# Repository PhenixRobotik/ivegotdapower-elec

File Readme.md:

# IveGotDaPower, dépôt électronique

Carte alimentation de PhenixRobotik pour la base roulante TheySeeMeRolling.

<div class="alert alert-warning">
    #This project requires KiCAD 5.0 and is not compatible with previous versions (software and libraries).
</div>

# Features

* Dual power input with no-cut switch
  * Battery 6S (24V max)
  * Power supply

* Multiple power outputs
  * Power (direct, 6A)
  * Elec (7.5V ~3A)
  * USB (for Rpi, 2A)
  * …

* Voltage + current instrumentations

* CAN bus

# Idées

* stm32f3
* LiPoBipper (équilibrage) ? (ou direct sur la batterie == plus safe ?)

* Bouton d'arrêt d'urgence qui coupe la puissance moteurs ?

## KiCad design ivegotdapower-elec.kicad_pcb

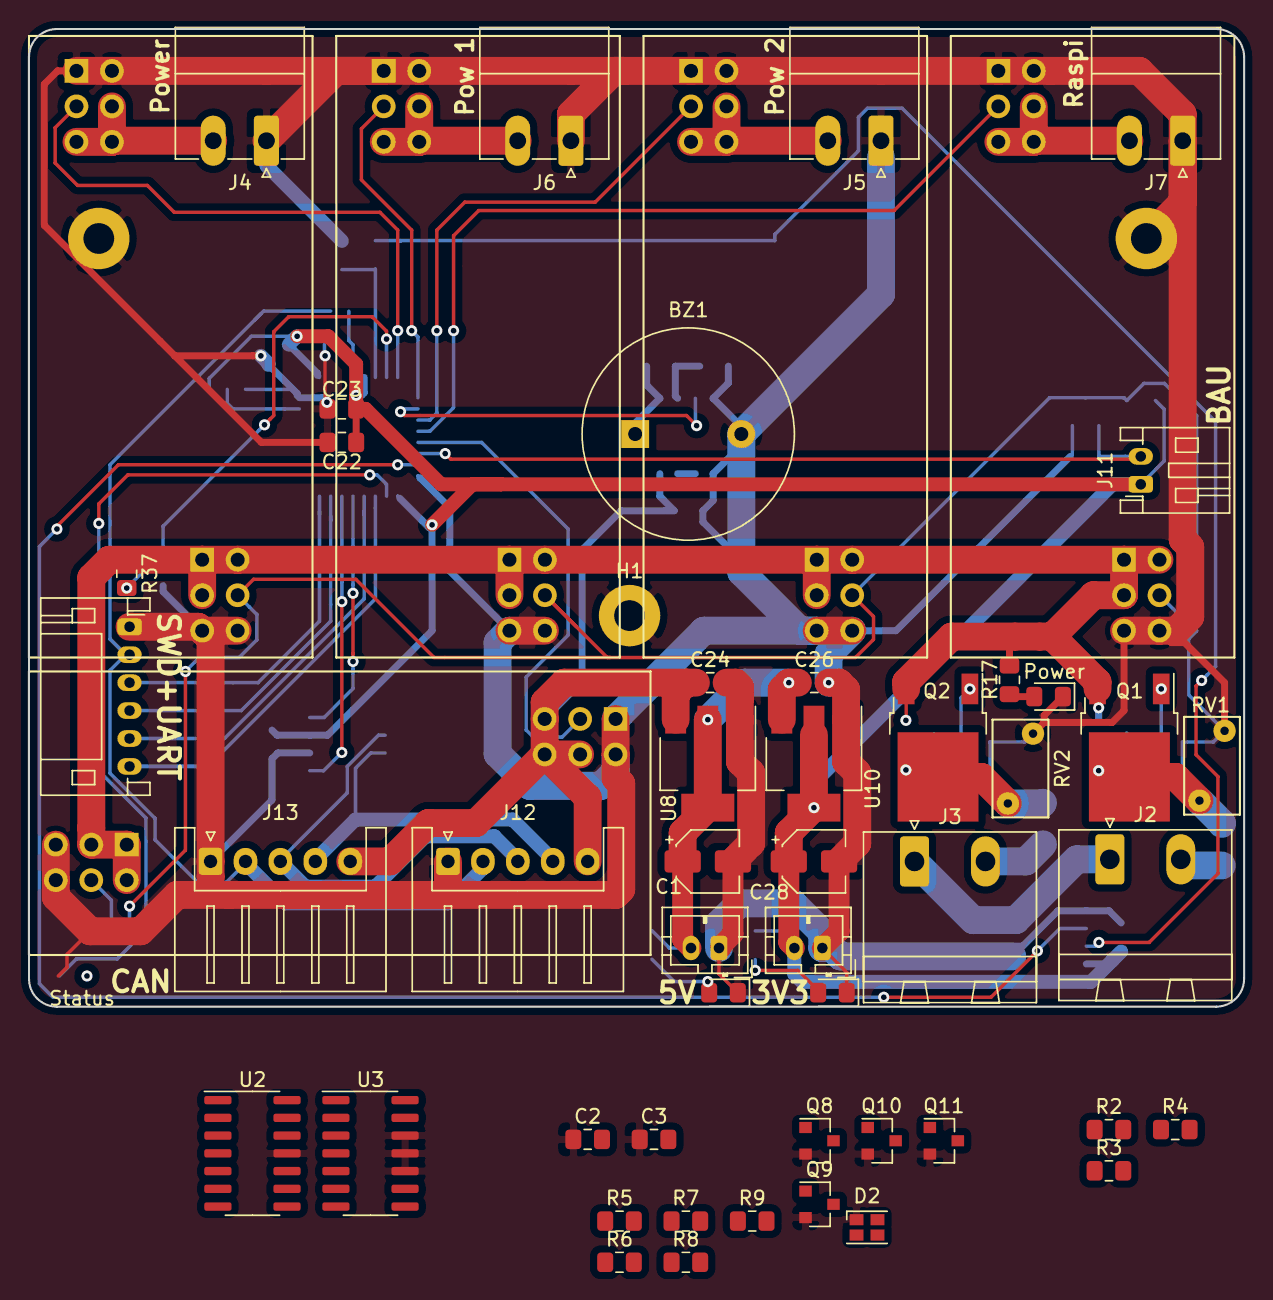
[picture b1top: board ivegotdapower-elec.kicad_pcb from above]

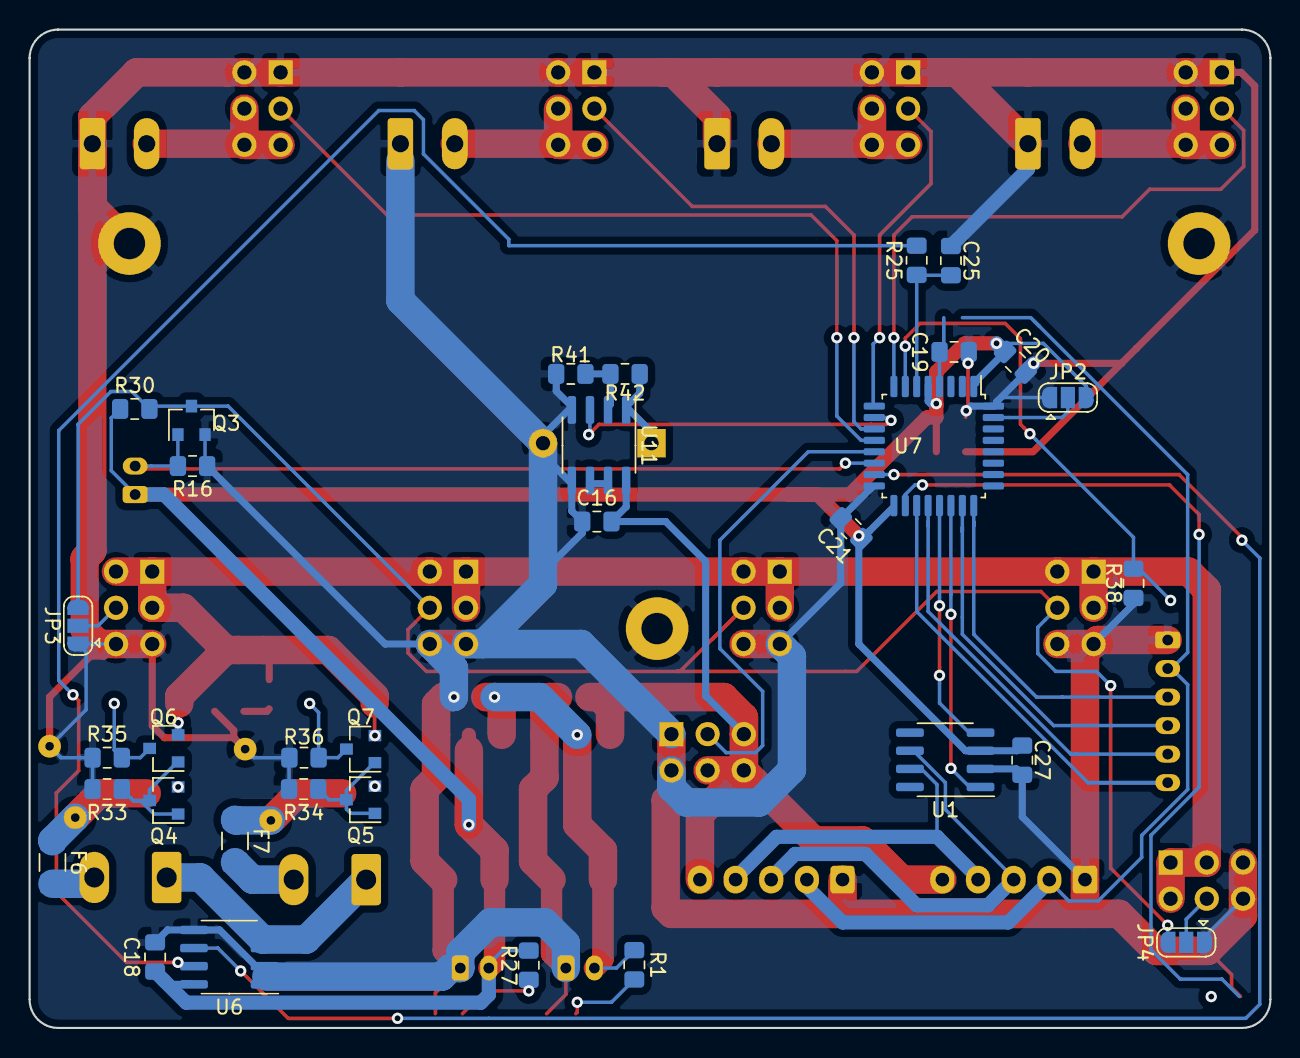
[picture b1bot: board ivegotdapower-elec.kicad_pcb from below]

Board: 2 copper layers, 87.0 x 70.0 mm, 88 parts (33 on the bottom side), 66 nets.

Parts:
B1, B2, B3, B4, B5: board_fille
BZ1: Buzzer; Buzzer_15x7.5RM7.6
C1, C28: 10uF; CP_Elec_4x5.4
C2, C3, C16, C18, C19, C20, C21, C23, C24, C25, C26, C27: 100nF; C_0805_2012Metric_Pad1.15x1.40mm_HandSolder
C22: 4.7uF; C_0805_2012Metric_Pad1.15x1.40mm_HandSolder
D1, D12, D16: LED; LED_0805_2012Metric_Pad1.15x1.40mm_HandSolder
D2: LED_ARGB; LED_Cree-PLCC4_2x2mm_CW
F6, F7: Fuse; Fuse_1206_3216Metric_Pad1.42x1.75mm_HandSolder
H1, H2, H3: MountingHole_Pad; MountingHole_2.2mm_M2_Pad
J1: Conn_Debug; JST_PH_S6B-PH-K_1x06_P2.00mm_Horizontal
J2: Conn_batt; PhoenixContact_MSTBA_2,5_2-G-5,08_1x02_P5.08mm_Horizontal
J3: Conn_alim; PhoenixContact_MSTBA_2,5_2-G-5,08_1x02_P5.08mm_Horizontal
J4: Conn_TSMR; PhoenixContact_MC_1,5_2-G-3.81_1x02_P3.81mm_Horizontal
J5: Conn_POW2; PhoenixContact_MC_1,5_2-G-3.81_1x02_P3.81mm_Horizontal
J6: Conn_POW1; PhoenixContact_MC_1,5_2-G-3.81_1x02_P3.81mm_Horizontal
J7: Conn_RPi; PhoenixContact_MC_1,5_2-G-3.81_1x02_P3.81mm_Horizontal
J8: Conn_+5V; JST_PH_B2B-PH-K_1x02_P2.00mm_Vertical
J10: Conn_+3.3V; JST_PH_B2B-PH-K_1x02_P2.00mm_Vertical
J11: Conn_bau; JST_PH_S2B-PH-K_1x02_P2.00mm_Horizontal
J12, J13: CAN_conn; JST_XH_S05B-XH-A_1x05_P2.50mm_Horizontal
JP2, JP3, JP4: Jumper_NC_Dual; SolderJumper-3_P1.3mm_Open_RoundedPad1.0x1.5mm
Q1, Q2: IRFR5305; TO-252-2
Q3, Q8, Q9, Q10, Q11: BSS138; SOT-23
Q4, Q5, Q6, Q7: MMBT2907A; SOT-23
R1, R17, R25, R27, R30, R33, R34, R35, R36, R41, R42: R; R_0805_2012Metric_Pad1.15x1.40mm_HandSolder
R2: 91; R_0805_2012Metric_Pad1.15x1.40mm_HandSolder
R3: 27; R_0805_2012Metric_Pad1.15x1.40mm_HandSolder
R4: 39; R_0805_2012Metric_Pad1.15x1.40mm_HandSolder
R5, R6, R7, R8, R9: 10k; R_0805_2012Metric_Pad1.15x1.40mm_HandSolder
R16: 1k; R_0805_2012Metric_Pad1.15x1.40mm_HandSolder
R37: 75k; R_0805_2012Metric_Pad1.15x1.40mm_HandSolder
R38: 15k; R_0805_2012Metric_Pad1.15x1.40mm_HandSolder
RV1, RV2: Varistor; RV_Disc_D7mm_W4mm_P5mm
U1: TCAN332; SOIC-8_3.9x4.9mm_P1.27mm
U2, U3: LM324; SOIC-14_3.9x8.7mm_P1.27mm
U6: ACS711xLCTR-12AB; SOIC-8_3.9x4.9mm_P1.27mm
U7: STM32F303K8Tx; LQFP-32_7x7mm_P0.8mm
U8: LD1117S50TR; SOT-223-3_TabPin2
U10: LD1117S33TR; SOT-223-3_TabPin2
U11: LM358; SOIC-8_3.9x4.9mm_P1.27mm

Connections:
+3V3: C18.1, C20.1, C21.1, C22.1, C23.1, C27.2, C28.1, J10.2, J11.1, JP2.3, R5.1, R6.1, R7.1, R8.1, R9.1, R27.1, R30.1, U1.3, U6.8, U7.1, U7.5, U7.17, U10.2
+5V: C1.1, C2.2, C3.2, C26.1, J8.2, R1.1, U2.4, U3.4, U8.2, U10.3
+7.5V: B2.10, B2.11, B2.12, C16.2, C24.1, J12.5, J13.5, U8.3, U11.8
/STM32/Buzzer: U7.10, U11.3
/STM32/CAN_RX: U1.4, U7.21
/STM32/CAN_TX: U1.1, U7.22
/STM32/RX_1: J1.5, U7.20
/STM32/TCK: J1.3, U7.24
/STM32/TMS: J1.4, U7.23
/STM32/TX_1: J1.6, U7.19
/STM32/mes_current: R25.1, U6.7
/STM32/mes_current_fault: U6.6, U7.15
/STM32/mes_protected_TSMR: U2.6, U2.7, U7.8
/STM32/mes_protected_logic: U3.6, U3.7, U7.13
/STM32/mes_protected_pow1: U2.8, U2.9, U7.9
/STM32/mes_protected_pow2: U2.13, U2.14, U7.11
/STM32/mes_protected_raw: U2.1, U2.2, U7.7
/STM32/mes_protected_rpi: U3.1, U3.2, U7.12
/STM32/mes_raw: R37.2, R38.1, U2.3
/STM32/reset_can: J12.2, J13.2, Q8.1, R5.2
/STM32/reset_logic/Reset_MCU: C19.1, Q9.3, Q11.3, R7.2, U7.4
/STM32/reset_swd: J1.2, Q10.1, R8.2
/buck/Logic_mes: B2.9, U3.5
/buck/Pow1_mes: B3.9, U2.10
/buck/Pow2_mes: B4.9, U2.12
/buck/RPi_mes: B1.9, U3.3
/buck/TSMR_mes: B5.9, U2.5
/buck/bau: J11.2, Q3.1, R16.1, U7.14
/buck/~on~-off: B3.4, B4.4, B5.4, JP3.3, JP4.3, Q3.3, R30.2
/power_selection/Valim+: F7.2, J3.2
/power_selection/Vbatt+: F6.2, J2.2
/power_selection/gnd_alims: J2.1, J3.1, U6.3, U6.4
GND: B1.5, B1.6, B1.7, B1.8, B2.5, B2.6, B2.7, B2.8, B3.5, B3.6, B3.7, B3.8, B4.5, B4.6, B4.7, B4.8, B5.5, B5.6, B5.7, B5.8, BZ1.2, C1.2, C2.1, C3.1, C16.1, C18.2, C19.2, C20.2, C21.2, C22.2, C23.2, C24.2, C25.1, C26.2, C27.1, C28.2, D1.1, D2.1, D12.1, D16.1, H1.1, H2.1, H3.1, J1.1, J4.1, J5.1, J6.1, J7.1, J8.1, J10.1, J12.1, J13.1, JP2.1, JP3.1, JP4.1, Q3.2, Q8.2, Q9.2, Q10.2, Q11.2, R16.2, R33.2, R34.2, R35.2, R36.2, R38.2, R41.1, RV1.2, RV2.2, U1.2, U2.11, U3.10, U3.11, U3.12, U6.1, U6.2, U6.5, U7.16, U7.32, U8.1, U10.1, U11.4, U11.5
IN: B1.1, B1.2, B1.3, B2.1, B2.2, B2.3, B3.1, B3.2, B3.3, B4.1, B4.2, B4.3, B5.1, B5.2, B5.3, Q1.3, Q2.3, Q6.2, Q7.2, R17.1, R37.1
unnamed: B1.4, JP3.2
unnamed: B1.10, B1.11, B1.12, J7.2
unnamed: B2.4, JP4.2
unnamed: B3.10, B3.11, B3.12, J6.2
unnamed: B4.10, B4.11, B4.12, J5.2
unnamed: B5.10, B5.11, B5.12, J4.2
unnamed: BZ1.1, R42.2, U11.1
unnamed: C25.2, R25.2, U7.6
unnamed: D1.2, R1.2
unnamed: D2.2, R2.2
unnamed: D2.3, R3.2
unnamed: D2.4, R4.2
unnamed: D12.2, R17.2
unnamed: D16.2, R27.2
unnamed: F6.1, Q1.2, Q4.2, RV1.1
unnamed: F7.1, Q2.2, Q5.2, RV2.1
unnamed: J12.3, J13.3, U1.6
unnamed: J12.4, J13.4, U1.7
unnamed: JP2.2, U7.31
unnamed: Q1.1, Q6.3, R35.1
unnamed: Q2.1, Q7.3, R36.1
unnamed: Q4.1, Q4.3, Q6.1, R33.1
unnamed: Q5.1, Q5.3, Q7.1, R34.1
unnamed: Q8.3, Q9.1, R6.2
unnamed: Q10.3, Q11.1, R9.2
unnamed: R2.1, U7.28
unnamed: R3.1, U7.29
unnamed: R4.1, U7.30
unnamed: R41.2, R42.1, U11.2
unnamed: U3.8, U3.9
unnamed: U3.13, U3.14
unnamed: U11.6, U11.7

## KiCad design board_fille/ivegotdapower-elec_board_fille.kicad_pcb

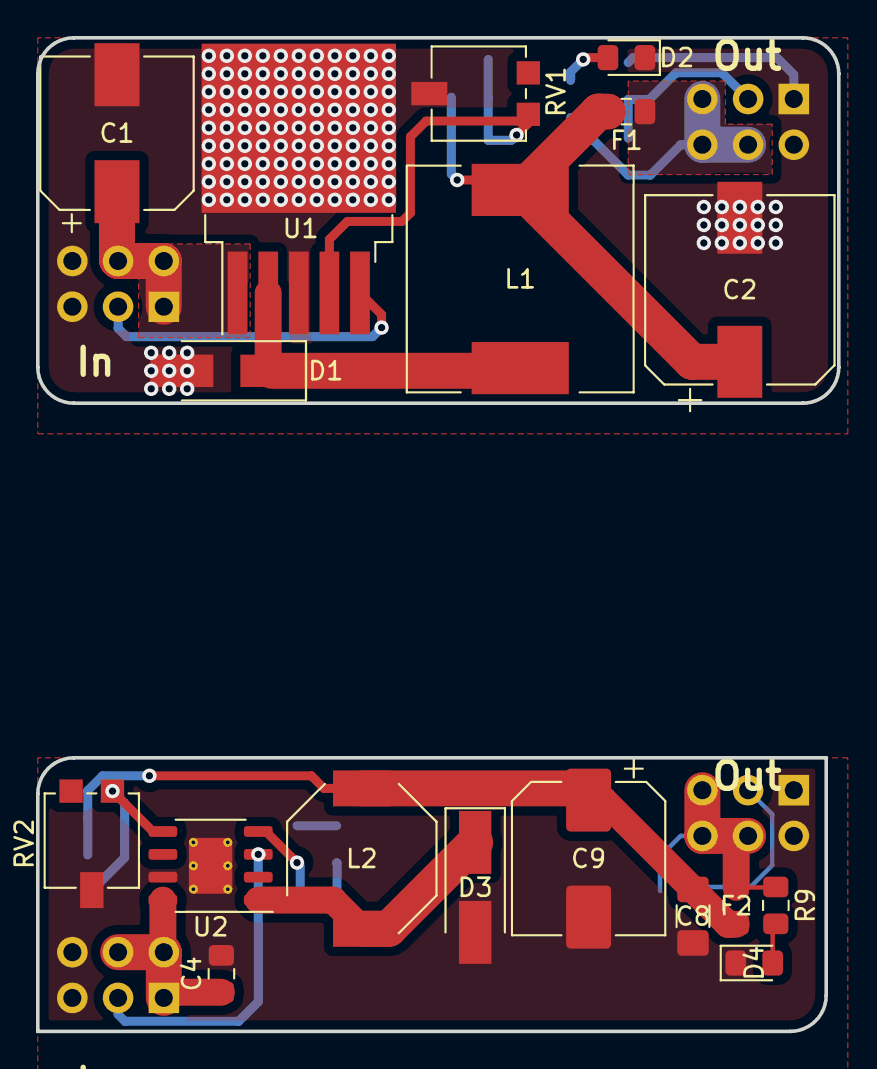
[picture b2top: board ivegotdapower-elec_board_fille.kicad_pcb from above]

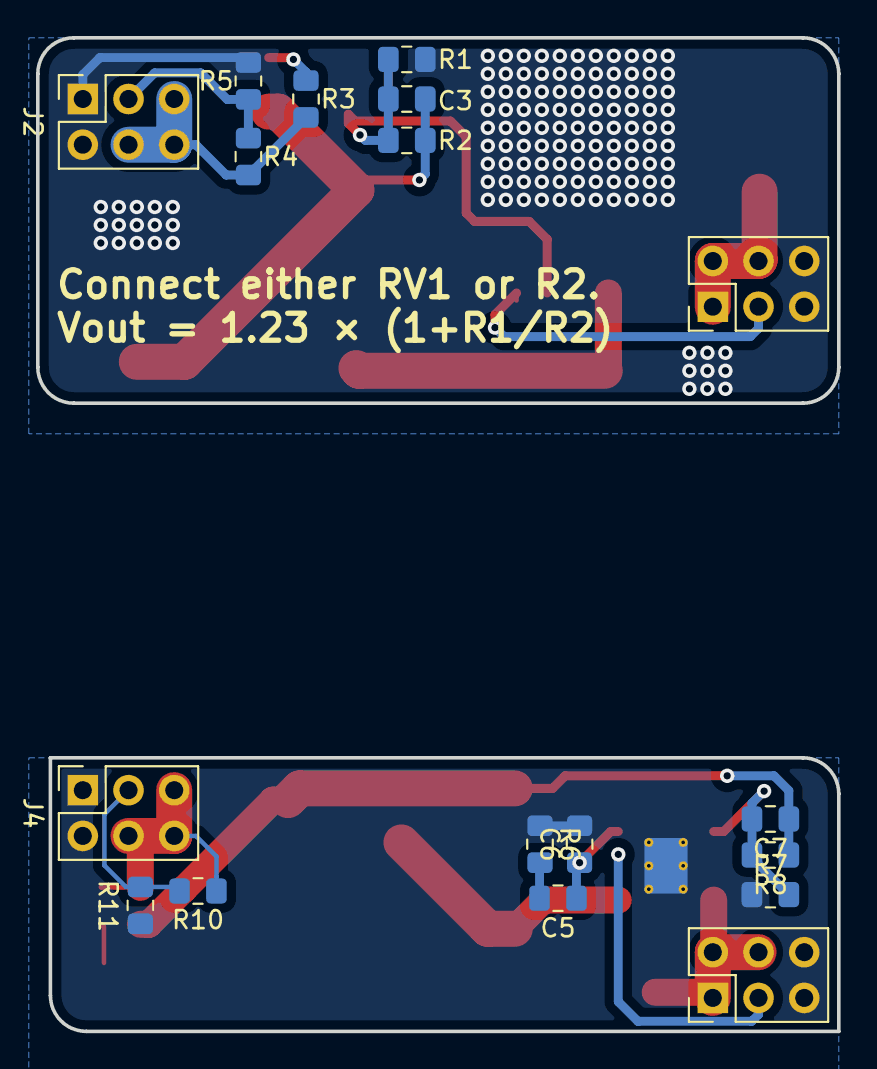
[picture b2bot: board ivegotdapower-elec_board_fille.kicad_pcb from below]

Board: 2 copper layers, 44.5 x 55.2 mm, 36 parts (18 on the bottom side), 15 nets.

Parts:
C1: 100uF; CP_Elec_8x10
C2: 220uF; CP_Elec_10x10
C3, C7: 15nF; C_0805_2012Metric_Pad1.15x1.40mm_HandSolder
C4: 10uF; C_0805_2012Metric_Pad1.15x1.40mm_HandSolder
C5: 22nF; C_0805_2012Metric_Pad1.15x1.40mm_HandSolder
C6: 220pF; C_0805_2012Metric_Pad1.15x1.40mm_HandSolder
C8: C; C_1206_3216Metric_Pad1.42x1.75mm_HandSolder
C9: 330uF; CP_Elec_8x10
D1, D3: D_Schottky 3A 40V; D_SMA_Handsoldering
D2, D4: LED; LED_0805_2012Metric_Pad1.15x1.40mm_HandSolder
F1, F2: Fuse; Fuse_0805_2012Metric_Pad1.15x1.40mm_HandSolder
J1, J3: Conn_02x03_Odd_Even; PinHeader_2x03_P2.54mm_Vertical
J2, J4: Conn_02x03_Odd_Even; PinSocket_2x03_P2.54mm_Vertical
L1: 33uH; L_12x12mm_H8mm
L2: 15uH; L_Bourns-SRU8043
R1, R7: 1k; R_0805_2012Metric_Pad1.15x1.40mm_HandSolder
R2, R8: 3.1k; R_0805_2012Metric_Pad1.15x1.40mm_HandSolder
R3, R4, R5, R9, R10, R11: R; R_0805_2012Metric_Pad1.15x1.40mm_HandSolder
R6: 4k7; R_0805_2012Metric_Pad1.15x1.40mm_HandSolder
RV1, RV2: R_POT; Potentiometer_Vishay_TS53YL_Vertical
U1: LM2596S-ADJ; TO-263-5_TabPin3
U2: L5973D; HSOP-8-1EP_3.9x4.9mm_P1.27mm_EP2.41x3.1mm_ThermalVias

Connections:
/Power_Input: C1.1, C4.1, J1.1, J1.2, J1.4, J3.1, J3.2, J3.4, U1.1, U2.8
/Power_Output: F1.1, F2.1, J2.4, J2.5, J2.6, J4.4, J4.5, J4.6, R3.1, R4.1, R9.1, R10.1
/on-off: J1.3, J3.3, U1.5, U2.3
/voltage_measure: J2.3, J4.3, R4.2, R5.1, R10.2, R11.1
GND: C1.2, C2.2, C4.2, C6.2, C8.2, C9.2, D1.2, D2.1, D3.2, D4.1, J1.5, J1.6, J2.1, J2.2, J3.5, J3.6, J4.1, J4.2, R1.1, R5.2, R6.1, R7.1, R11.2, RV1.2, RV2.2, U1.3, U2.7, U2.9
unnamed: C2.1, C3.1, F1.2, L1.2, R2.1
unnamed: C3.2, R1.2, R2.2, RV1.3, U1.4
unnamed: C5.1, C6.1, U2.4
unnamed: C5.2, R6.2
unnamed: C7.1, C8.1, C9.1, F2.2, L2.2, R8.1
unnamed: C7.2, R7.2, R8.2, RV2.3, U2.5
unnamed: D1.1, L1.1, U1.2
unnamed: D2.2, R3.2
unnamed: D3.1, L2.1, U2.1
unnamed: D4.2, R9.2

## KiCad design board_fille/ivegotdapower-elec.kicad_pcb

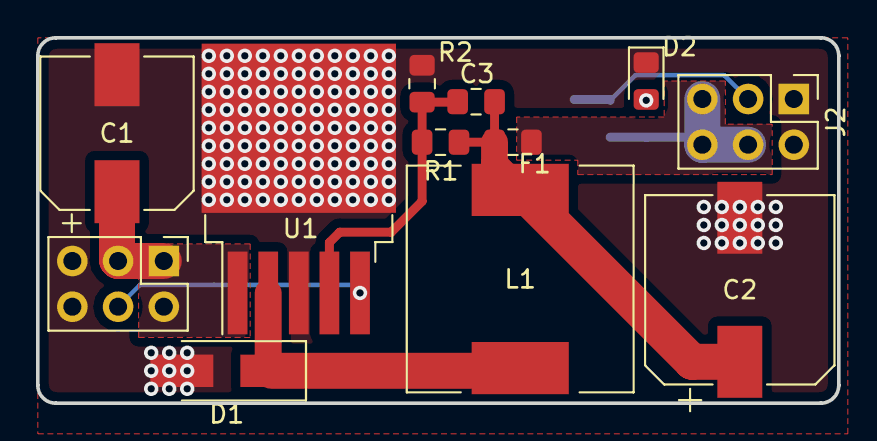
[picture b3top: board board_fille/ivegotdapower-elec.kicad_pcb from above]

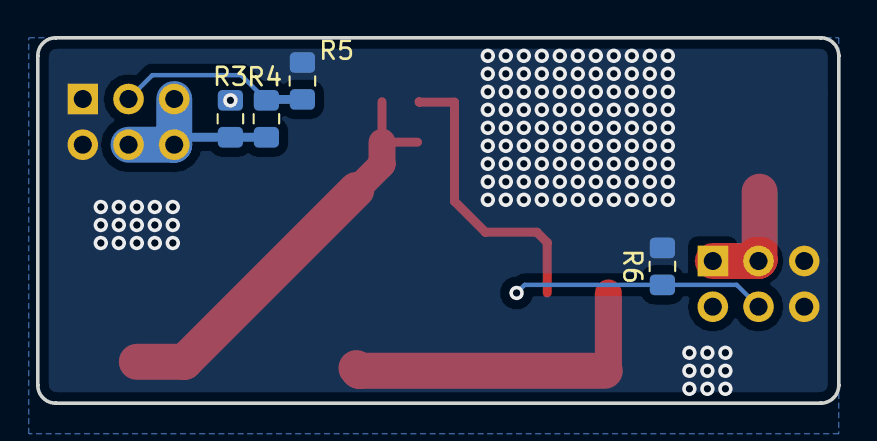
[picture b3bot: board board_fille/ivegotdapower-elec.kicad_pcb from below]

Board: 2 copper layers, 44.5 x 20.3 mm, 16 parts (4 on the bottom side), 9 nets.

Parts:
C1: 100uF; CP_Elec_8x10
C2: 220uF; CP_Elec_10x10
C3: 15nF; C_0805_2012Metric_Pad1.15x1.40mm_HandSolder
D1: D_Schottky 3A 40V; D_SMA_Handsoldering
D2: LED; LED_0805_2012Metric_Pad1.15x1.40mm_HandSolder
F1: Fuse; Fuse_0805_2012Metric_Pad1.15x1.40mm_HandSolder
J1, J2: Conn_02x03_Odd_Even; PinHeader_2x03_P2.54mm_Vertical
L1: 33uH; L_12x12mm_H8mm
R1: 3.1k; R_0805_2012Metric_Pad1.15x1.40mm_HandSolder
R2: 1k; R_0805_2012Metric_Pad1.15x1.40mm_HandSolder
R3, R4, R5, R6: R; R_0805_2012Metric_Pad1.15x1.40mm_HandSolder
U1: LM2596S-ADJ; TO-263-5_TabPin3

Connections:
/Power_Input: C1.1, J1.1, J1.2, J1.3, U1.1
/Power_Output: F1.1, J2.4, J2.5, J2.6, R3.1, R4.1
/on-off: J1.4, R6.1, U1.5
/voltage_measure: J2.3, R4.2, R5.1
GND: C1.2, C2.2, D1.2, D2.1, J1.5, J1.6, J2.1, J2.2, R2.1, R5.2, R6.2, U1.3
unnamed: C2.1, C3.1, F1.2, L1.2, R1.1
unnamed: C3.2, R1.2, R2.2, U1.4
unnamed: D1.1, L1.1, U1.2
unnamed: D2.2, R3.2

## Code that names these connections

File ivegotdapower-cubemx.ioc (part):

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Mcu.Name=STM32F303K(6-8)Tx
Mcu.Package=LQFP32
Mcu.UserName=STM32F303K8Tx
PA0.GPIOParameters=GPIO_Label
PA0.GPIO_Label=ADC_IN1 [SENSE]
PA0.Mode=IN1-Single-Ended
PA0.Signal=ADC1_IN1
PA1.GPIOParameters=GPIO_Label
PA1.GPIO_Label=ADC1_IN2 [RPI]
PA1.Mode=IN2-Single-Ended
PA1.Signal=ADC1_IN2
PA10.Mode=Asynchronous
PA10.Signal=USART1_RX
PA11.Mode=Master
PA11.Signal=CAN_RX
PA12.Mode=Master
PA12.Signal=CAN_TX
PA13.Mode=Serial_Wire
PA13.Signal=SYS_JTMS-SWDIO
PA14.Mode=Serial_Wire
PA14.Signal=SYS_JTCK-SWCLK
PA2.GPIOParameters=GPIO_Label
PA2.GPIO_Label=ADC1_IN3 [RAW]
PA2.Mode=IN3-Single-Ended
PA2.Signal=ADC1_IN3
PA3.GPIOParameters=GPIO_Label
PA3.GPIO_Label=ADC1_IN4 [LOGIC]
PA3.Mode=IN4-Single-Ended
PA3.Signal=ADC1_IN4
PA4.GPIOParameters=GPIO_Label
PA4.GPIO_Label=DAC1_OUT1 [BUZZER]
PA4.Signal=COMP_DAC11_group
PA5.GPIOParameters=GPIO_Label
PA5.GPIO_Label=ADC2_IN2 [POW1]
PA5.Mode=IN2-Single-Ended
PA5.Signal=ADC2_IN2
PA6.GPIOParameters=GPIO_Label
PA6.GPIO_Label=ADC2_IN3 [POW2]
PA6.Mode=IN3-Single-Ended
PA6.Signal=ADC2_IN3
PA7.GPIOParameters=GPIO_Label
PA7.GPIO_Label=ADC2_IN4 [TSMR]
PA7.Mode=IN4-Single-Ended
PA7.Signal=ADC2_IN4
PA8.GPIOParameters=GPIO_Label
PA8.GPIO_Label=LED
PA8.Signal=GPIO_Output
PA9.Mode=Asynchronous
PA9.Signal=USART1_TX
PB0.GPIOParameters=GPIO_Label
PB0.GPIO_Label=BAU
PB0.Signal=GPIO_Input
PB1.GPIOParameters=GPIO_Label
PB1.GPIO_Label=FAULT
PB1.Signal=GPIO_Input
RCC.HSEPLLFreq_Value=8000000
RCC.HSE_VALUE=8000000
RCC.SYSCLKFreq_VALUE=8000000
board=custom

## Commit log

2018-06-11 Add gitignore, add some schematics
2018-06-13 Add phenix_kicad libraries
2018-06-13 Add power sources switch
2018-06-17 move, add input protections
2018-06-17 Add outline for 5×5cm / 10×5cm
2018-06-18 Footprint Association
2018-06-18 Change LTC4353 symbol (MSOP), change MOSFET symbols and footprints.
2018-06-18 Add most of interesting components.
2018-07-11 update submodule
2018-07-11 Add can connectors, power input/output connectors. Fix labels/power symbols. Remove schottky diodes, use NMOS on base instead.
2018-07-11 Add connectors, power footprints. Not sure of all footprints.
2018-07-11 Small reorganization. There is space left for stm32.
2018-10-03 power regulators added
2018-10-03 +5V and +3.3V added in case of PLS and connector for power selection
2018-10-03 Reorganize buck
2018-10-03 Set footprints, cleanup PCB of old componnents
2018-10-04 buzzer and mes
2018-10-04 varistor added
2018-10-04 decoupling
2018-10-08 Add daughter power board
2018-10-09 fixed ideal diode
2018-10-09 cleanup, finished design
2018-10-09 fixed bad connexion
2018-10-10 very small changes in fille
2018-10-10 Add board_fille libraries
2018-10-10 level translation
2018-10-24 jumper error corrected
2018-10-24 power routed
2018-10-25 update board_fille
2018-10-25 bords ronds
2018-10-30 Update phenix_kicad
2018-11-01 update sym libs
2018-11-02 Added CubeMX project
2018-11-02 Update schematics
2018-11-02 Placement and routing done
2018-11-02 Fixed phenix_kicad name
2018-11-02 Improvements on GND nets
2018-11-04 Sérigraphie
2018-11-04 Sérigraphies
2018-11-05 Silkscreen, better pcb
2018-11-05 Connect mountholes to GND, silkscreen
2018-11-05 Board cleanup, reorganize
2018-11-05 small cleanup
2018-11-05 Moved MC connectors
2018-11-07 Changed LED footprints
2018-11-07 Changed fuse footprint
2018-11-09 some weird changes.
2018-11-12 Rename sub-board
2019-06-04 Add potentiometer to board. Move SMD further apart.
2019-06-05 add text below pcb
2019-06-07 Add possible variant for board fille
2019-11-05 Update gitignore
2019-11-05 Refactoring. Add protection (OpAmps) on analog measures
2019-11-05 Backport Bss138-powered reset separation
2019-11-05 Rewrite board_fille symbol
2019-11-05 Fix libs
2019-11-11 fixes and new regulator type
2019-11-11 schematics for new version done
2019-11-11 added vmos external acess in case of need
